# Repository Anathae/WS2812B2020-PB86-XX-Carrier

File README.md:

# WS2812B2020-PB86-XX-Carrier
 Carrier for one or two WS2812B2020 for the PB86-XX switches.

# A brief history
 On 2022-07-27, Adafruit released their new products video on YouTube announcing that they were now carrying the PB86-A1 1P2T switch with LED.  In the first week of August 2022, I stumbled accross this video, amongst others, and was inspired to create this project.

# Background
 This project references PB86-XX switches.  From what I have been able to glean, this is actually a range of switches that appear to come in a number of colors, two different "key top" widths, and from zero to two 3mm LED.  As of writing of this document
 Adafruit was carrying only the PB86-A1 switch.  One of the videos I watched was the JP's Product PICK OF THE WEEK where JP introduces the PB86-A1.  A commentor in the Adafruit discord suggested finding a four lead, 3mm RBG LED that could be used with the switch.
 This is my attempt to push that along.

# Design
 As I am interested in DIY mechanical keyboards, I was interested in having both a version of this switch that was better suited to the 19.05mm spacing of a standard keyboard, and having the maximum flexiability in how many of a particular LED were available
 for flashy animations.  During my research on the PB86-A1 switch, I discovered the wider version of this switch, as well as the fact that it came in zero, one, or two LED variations of both widths, as well as a range of keytop colors.

# Implimentation
 My current design allows for a four pin surface mount header on the bottom of the carrier with +5 (VDD), DI (DIN), DO (DOUT), and GND (VSS) pins, as well as solder pads on the top that allow the mounting of one or two of the WS2812B2020 device.  DOUT of LED 1 is connected
 to DIN of LED 2, and DIN and DOUT of LED 3 are connected to the header on the other side of the PCB.  The intent is to populate only the outer two LEDs, or only the central LED.  Not having any of these switches on hand, I limited the PCB to the foot print of a 0.8mm solder
 pad for a 4 pin header and a wide enough for two 3mm LEDs.  From what I have seen in images, I think this will fit.  3mm LEDs, in my experience, have leads that are not as robust as standard 0.1" (2.54mm) spacing headers, and as such, the switch may require modification to allow
 the thicker leads of a more typical four pin header through the body of the switch.  Also, I was finding it difficult to find both a virtical mount header with leads long enough to pass through the switch as well as one that had only 3mm accross the long axis of the solder pads.  
 This may require custom pins for the leads.

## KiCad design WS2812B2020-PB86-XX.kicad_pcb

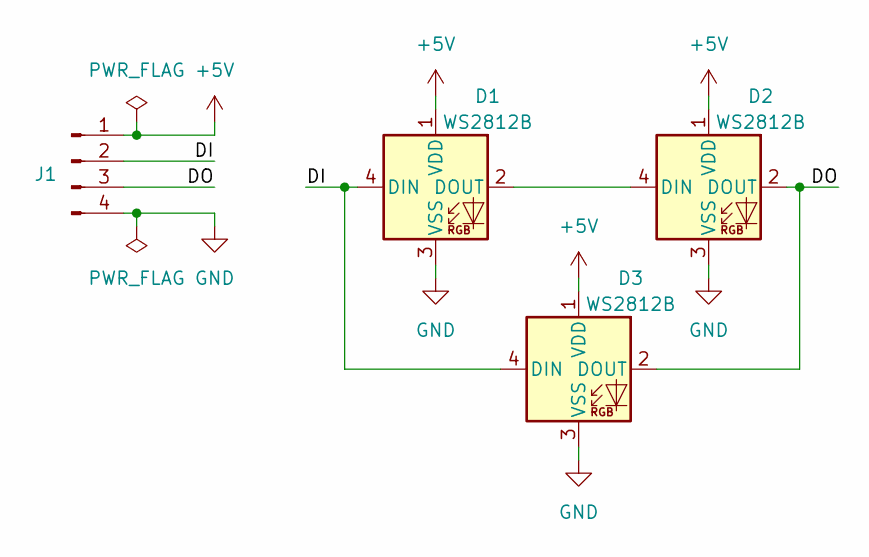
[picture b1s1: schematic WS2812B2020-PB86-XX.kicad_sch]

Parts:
D1, D2, D3: WS2812B; LED_WS2812B-2020_PLCC4_2.0x2.0mm
J1: Conn_01x04_Pin; PB86-XX-LEDCarrier

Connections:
+5V: D1.1 (VDD), D2.1 (VDD), D3.1 (VDD), J1.1
/DI: D1.4 (DIN), D3.4 (DIN), J1.2
/DO: D2.2 (DOUT), D3.2 (DOUT), J1.3
GND: D1.3 (VSS), D2.3 (VSS), D3.3 (VSS), J1.4
unnamed: D1.2 (DOUT), D2.4 (DIN)

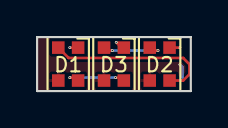
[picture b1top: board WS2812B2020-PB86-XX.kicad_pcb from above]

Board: 2 copper layers, 8.5 x 3.0 mm, 4 parts (0 on the bottom side), 5 nets.

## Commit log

2023-08-08 Initial push of files to github
    Initial push of files created in KiCad for carrier to github
2023-08-08 Update README.md
    Dump of what the project is, why I created it, and some initial concerns.
